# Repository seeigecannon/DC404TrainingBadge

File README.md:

# DC404TrainingBadge
DC404 Learn to Solder Badge

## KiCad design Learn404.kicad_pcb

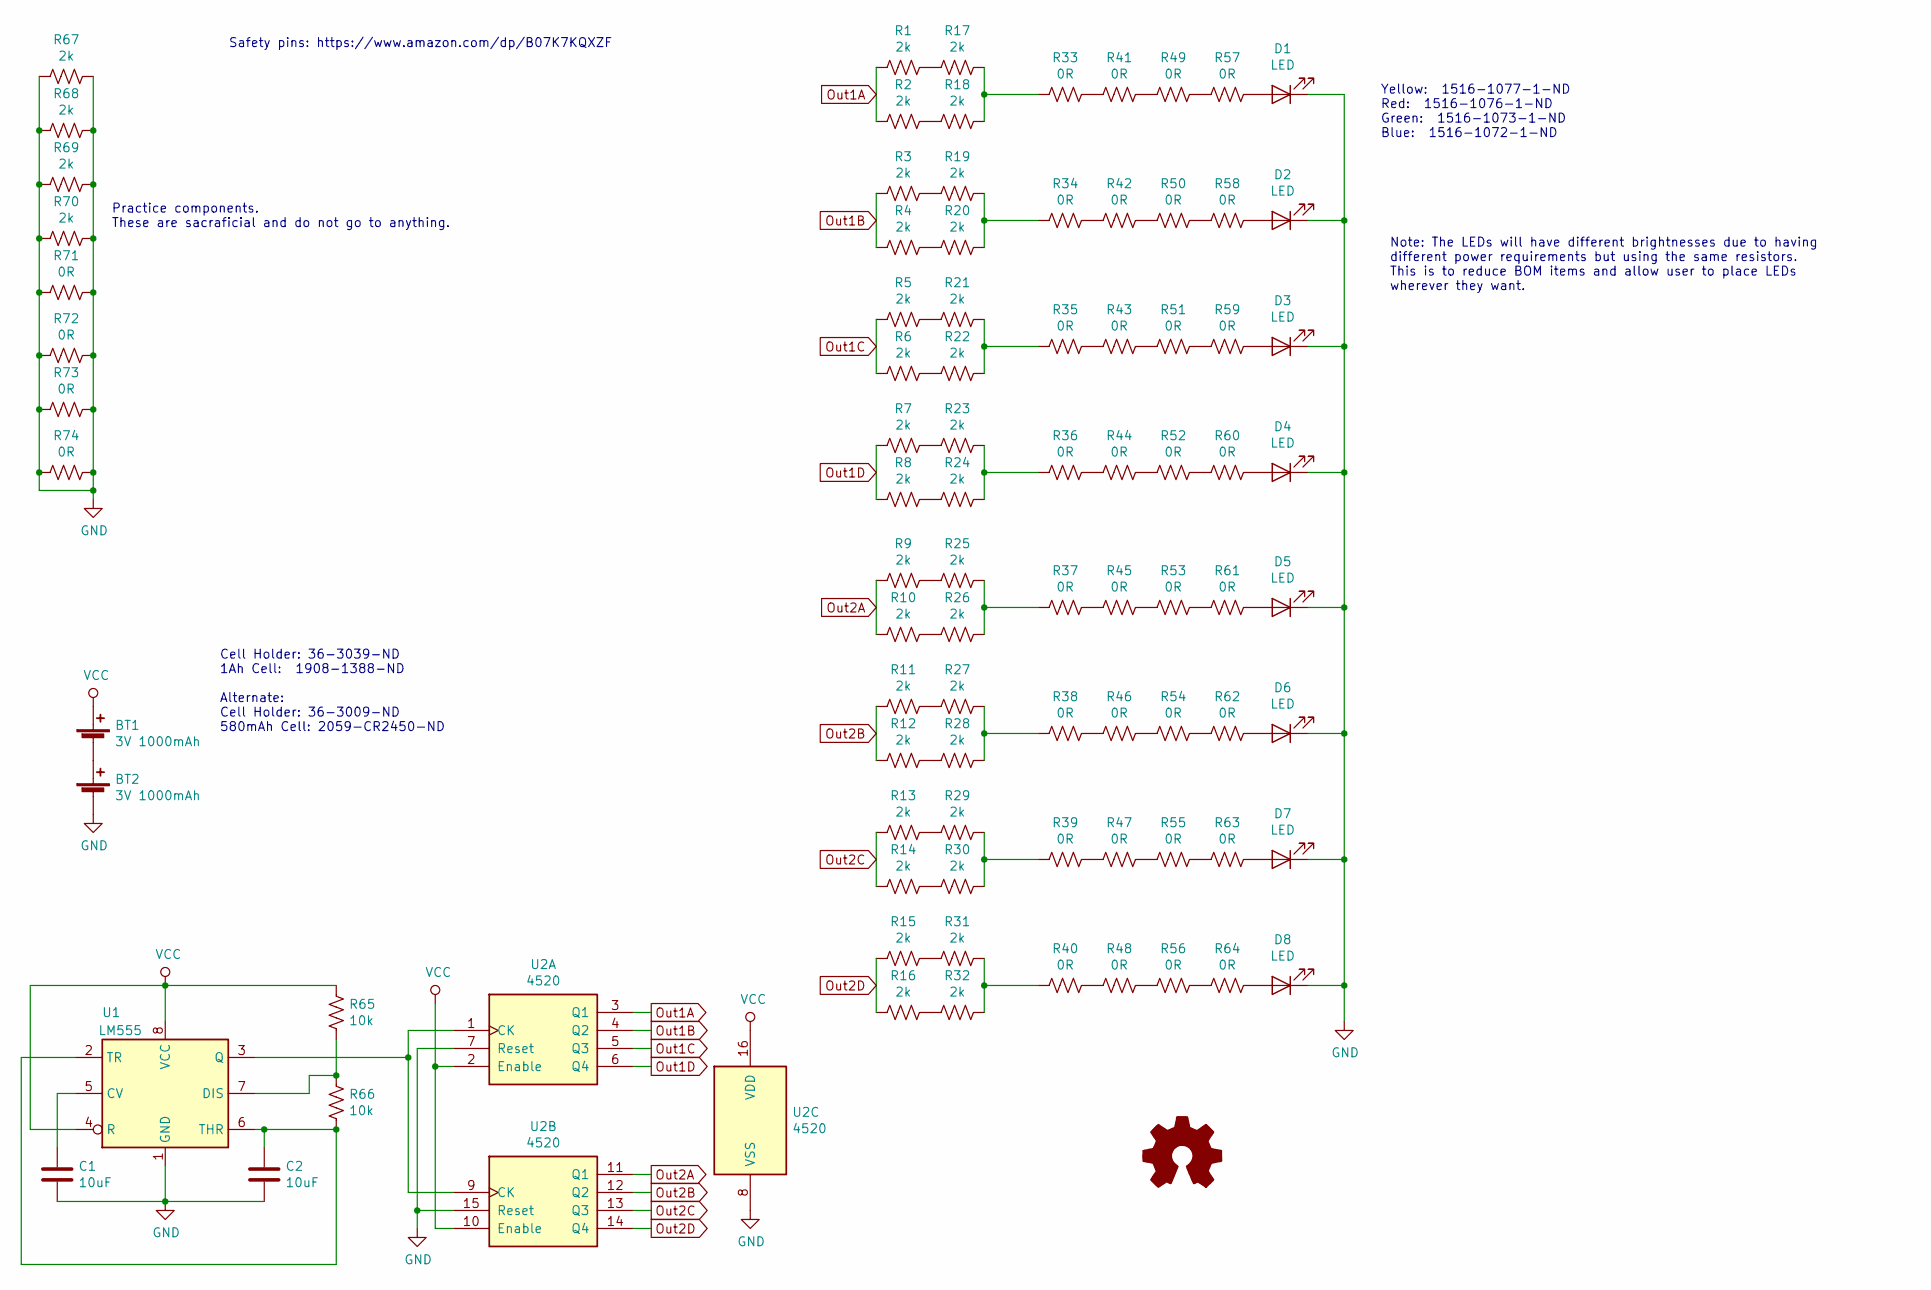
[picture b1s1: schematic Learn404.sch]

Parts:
BT1, BT2: 3V 1000mAh; BatteryHolder_Keystone_3009_1x2450; PartNum BCAAAPC-ND
C1, C2: 10uF; C_Disc_D10.5mm_W5.0mm_P5.00mm; PartNum FK26X7R1C106K
D1, D2, D3, D4, D5, D6, D7, D8: LED; R_1210_3225Metric_Pad1.42x2.65mm_HandSolder
R1, R2, R3, R4, R5, R6, R7, R8, R9, R10, R11, R12, R13, R14, R15, R16, R17, R18, R19, R20, R21, R22, R23, R24, R25, R26, R27, R28, R29, R30, R31, R32, R67, R68, R69, R70: 2k; R_Axial_DIN0207_L6.3mm_D2.5mm_P10.16mm_Horizontal; Part Number CF14JT2K00CT-ND
R33, R34, R35, R36, R37, R38, R39, R40, R41, R42, R43, R44, R45, R46, R47, R48, R49, R50, R51, R52, R53, R54, R55, R56, R57, R58, R59, R60, R61, R62, R63, R64, R71, R72, R73, R74: 0R; R_1206_3216Metric_Pad1.42x1.75mm_HandSolder; Part Number RMCF1206ZT0R00
R65, R66: 10k; R_Axial_DIN0207_L6.3mm_D2.5mm_P10.16mm_Horizontal; Part Number CF14JT10K0
U1: LM555; SOIC-8_3.9x4.9mm_P1.27mm; PartNum 296-21752-1-ND
U2: 4520; SOIC-16_3.9x9.9mm_P1.27mm; PartNum CD74HCT4520M

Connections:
GND: BT2.2 (-), C1.2, C2.2, D1.1 (K), D2.1 (K), D3.1 (K), D4.1 (K), D5.1 (K), D6.1 (K), D7.1 (K), D8.1 (K), R67.1, R67.2, R68.1, R68.2, R69.1, R69.2, R70.1, R70.2, R71.1, R71.2, R72.1, R72.2, R73.1, R73.2, R74.1, R74.2, U1.1 (GND), U2.7 (Reset), U2.8 (VSS), U2.15 (Reset)
unnamed: BT1.2 (-), BT2.1 (+)
unnamed: C1.1, U1.5 (CV)
unnamed: C2.1, R66.1, U1.2 (TR), U1.6 (THR)
unnamed: D1.2 (A), R57.1
unnamed: D2.2 (A), R58.1
unnamed: D3.2 (A), R59.1
unnamed: D4.2 (A), R60.1
unnamed: D5.2 (A), R61.1
unnamed: D6.2 (A), R62.1
unnamed: D7.2 (A), R63.1
unnamed: D8.2 (A), R64.1
unnamed: R1.1, R17.2
unnamed: R10.1, R26.2
unnamed: R11.1, R27.2
unnamed: R12.1, R28.2
unnamed: R13.1, R29.2
unnamed: R14.1, R30.2
unnamed: R15.1, R31.2
unnamed: R16.1, R32.2
unnamed: R17.1, R18.1, R33.2
unnamed: R2.1, R18.2
unnamed: R19.1, R20.1, R34.2
unnamed: R3.1, R19.2
unnamed: R4.1, R20.2
unnamed: R21.1, R22.1, R35.2
unnamed: R5.1, R21.2
unnamed: R6.1, R22.2
unnamed: R23.1, R24.1, R36.2
unnamed: R7.1, R23.2
unnamed: R8.1, R24.2
unnamed: R25.1, R26.1, R37.2
unnamed: R9.1, R25.2
unnamed: R27.1, R28.1, R38.2
unnamed: R29.1, R30.1, R39.2
unnamed: R31.1, R32.1, R40.2
unnamed: R33.1, R41.2
unnamed: R34.1, R42.2
unnamed: R35.1, R43.2
unnamed: R36.1, R44.2
unnamed: R37.1, R45.2
unnamed: R38.1, R46.2
unnamed: R39.1, R47.2
unnamed: R40.1, R48.2
unnamed: R41.1, R49.2
unnamed: R42.1, R50.2
unnamed: R43.1, R51.2
unnamed: R44.1, R52.2
unnamed: R45.1, R53.2
unnamed: R46.1, R54.2
unnamed: R47.1, R55.2
unnamed: R48.1, R56.2
unnamed: R49.1, R57.2
unnamed: R50.1, R58.2
unnamed: R51.1, R59.2
unnamed: R52.1, R60.2
unnamed: R53.1, R61.2
unnamed: R54.1, R62.2
unnamed: R55.1, R63.2
unnamed: R56.1, R64.2
unnamed: R65.1, R66.2, U1.7 (DIS)
unnamed: U1.3 (Q), U2.1 (CK), U2.9 (CK)
Out1A: R1.2, R2.2, U2.3 (Q1)
Out1B: R3.2, R4.2, U2.4 (Q2)
Out1C: R5.2, R6.2, U2.5 (Q3)
Out1D: R7.2, R8.2, U2.6 (Q4)
Out2A: R9.2, R10.2, U2.11 (Q1)
Out2B: R11.2, R12.2, U2.12 (Q2)
Out2C: R13.2, R14.2, U2.13 (Q3)
Out2D: R15.2, R16.2, U2.14 (Q4)
VCC: BT1.1 (+), R65.2, U1.4 (R), U1.8 (VCC), U2.2 (Enable), U2.10 (Enable), U2.16 (VDD)

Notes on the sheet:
Yellow: 1516-1077-1-ND Red: 1516-1076-1-ND Green: 1516-1073-1-ND Blue: 1516-1072-1-ND
Cell Holder: 36-3039-ND 1Ah Cell: 1908-1388-ND Alternate: Cell Holder: 36-3009-ND 580mAh Cell: 2059-CR2450-ND
Safety pins: https://www.amazon.com/dp/B07K7KQXZF
Practice components. These are sacraficial and do not go to anything.
Note: The LEDs will have different brightnesses due to having different power requirements but using the same resistors. This is to reduce BOM items and allow user to place LEDs wherever they want.

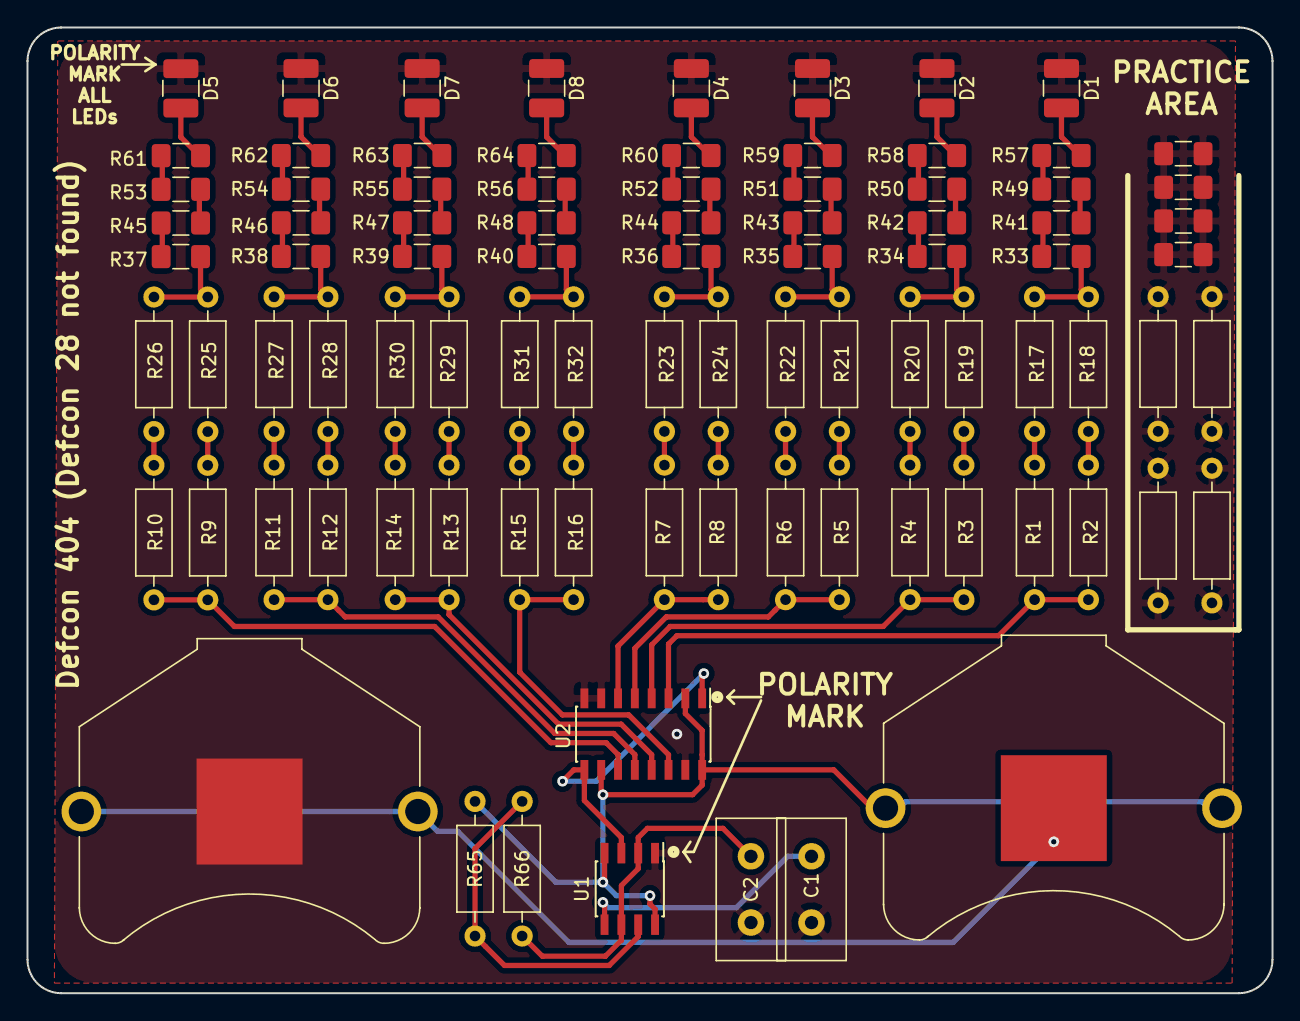
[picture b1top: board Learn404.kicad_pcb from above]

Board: 2 copper layers, 94.0 x 72.9 mm, 88 parts (0 on the bottom side), 71 nets.

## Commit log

2020-07-26 Initial upload
2021-06-22 Uploaded Rev B files. This board is known to work.
